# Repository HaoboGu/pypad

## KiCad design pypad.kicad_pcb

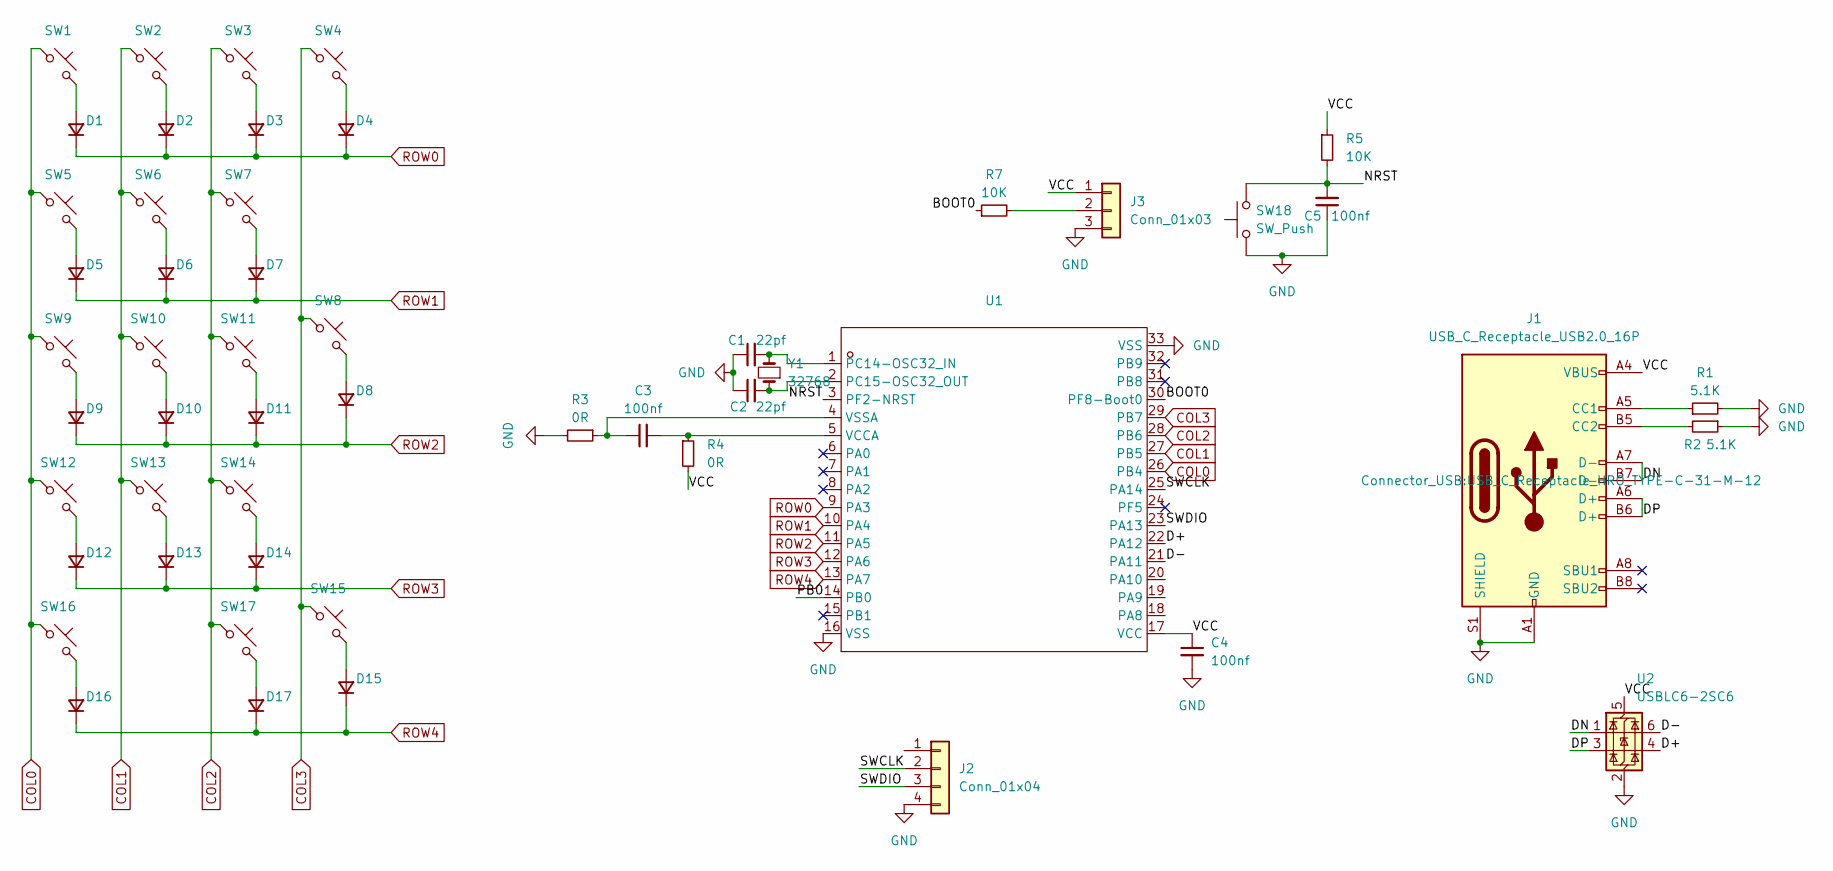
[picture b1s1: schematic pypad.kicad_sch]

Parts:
C1, C2: 22pf; C_0603_1608Metric
C3, C4, C5: 100nf; C_0603_1608Metric
D1, D2, D3, D4, D5, D6, D7, D8, D9, D10, D11, D12, D13, D14, D15, D16, D17: D; D_SOD-123F
J1: USB_C_Receptacle_USB2.0_16P; USB_C_Receptacle_HRO_TYPE-C-31-M-12
J2: Conn_01x04; PinHeader_1x04_P2.54mm_Vertical
J3: Conn_01x03; PinHeader_1x03_P2.54mm_Vertical
R1, R2: 5.1K; R_0603_1608Metric_Pad0.98x0.95mm_HandSolder
R3, R4: 0R; R_0603_1608Metric_Pad0.98x0.95mm_HandSolder
R5, R7: 10K; R_0603_1608Metric_Pad0.98x0.95mm_HandSolder
SW1, SW2, SW3, SW4, SW5, SW6, SW7, SW8, SW9, SW10, SW11, SW12, SW13, SW14, SW15, SW16, SW17: SW_Push; SW_Cherry_MX_PCB_1.00u
SW18: SW_Push; SW_SPST_PTS810
U1: QFN-32_L5.0-W5.0-P0.50-TL-EP3.5; Manufacturer Part PY32F071K1BU; LCSC Part Name PY32F071K1BU
U2: USBLC6-2SC6; SOT-23-6
Y1: 32768; Crystal_SMD_EuroQuartz_EQ161-2Pin_3.2x1.5mm

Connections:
/BOOT0: R7.1, U1.30 (PF8-Boot0)
/D+: U1.22 (PA12), U2.4 (I/O2)
/D-: U1.21 (PA11), U2.6 (I/O1)
/DN: J1.A7 (D-), J1.B7 (D-), U2.1 (I/O1)
/DP: J1.A6 (D+), J1.B6 (D+), U2.3 (I/O2)
/NRST: C5.2, R5.2, SW18.2, U1.3 (PF2-NRST)
/PB0: U1.14 (PB0)
/SWCLK: J2.2, U1.25 (PA14)
/SWDIO: J2.3, U1.23 (PA13)
/VCC: C4.1, J1.A4 (VBUS), J1.A9 (VBUS), J1.B4 (VBUS), J1.B9 (VBUS), J3.1, R4.2, R5.1, U1.17 (VCC), U2.5 (VBUS)
COL0: SW1.1, SW5.1, SW9.1, SW12.1, SW16.1, U1.26 (PB4)
COL1: SW2.1, SW6.1, SW10.1, SW13.1, U1.27 (PB5)
COL2: SW3.1, SW7.1, SW11.1, SW14.1, SW17.1, U1.28 (PB6)
COL3: SW4.1, SW8.1, SW15.1, U1.29 (PB7)
GND: C1.1, C2.1, C4.2, C5.1, J1.A1 (GND), J1.A12 (GND), J1.B1 (GND), J1.B12 (GND), J1.S1 (SHIELD), J2.4, J3.3, R1.2, R2.1, R3.2, SW18.1, U1.16 (VSS), U1.33 (VSS), U2.2 (GND)
unnamed: D1.2 (A), SW1.2
unnamed: D2.2 (A), SW2.2
unnamed: D3.2 (A), SW3.2
unnamed: D4.2 (A), SW4.2
unnamed: D5.2 (A), SW5.2
unnamed: D6.2 (A), SW6.2
unnamed: D7.2 (A), SW7.2
unnamed: D8.2 (A), SW8.2
unnamed: D9.2 (A), SW9.2
unnamed: D10.2 (A), SW10.2
unnamed: D11.2 (A), SW11.2
unnamed: D12.2 (A), SW12.2
unnamed: D13.2 (A), SW13.2
unnamed: D14.2 (A), SW14.2
unnamed: D15.2 (A), SW15.2
unnamed: D16.2 (A), SW16.2
unnamed: D17.2 (A), SW17.2
unnamed: J1.A5 (CC1), R1.1
unnamed: J1.B5 (CC2), R2.2
unnamed: J3.2, R7.2
unnamed: C1.2, U1.1 (PC14-OSC32_IN), Y1.2
unnamed: C2.2, U1.2 (PC15-OSC32_OUT), Y1.1
unnamed: C3.2, R4.1, U1.5 (VCCA)
unnamed: C3.1, R3.1, U1.4 (VSSA)
ROW0: D1.1 (K), D2.1 (K), D3.1 (K), D4.1 (K), U1.9 (PA3)
ROW1: D5.1 (K), D6.1 (K), D7.1 (K), U1.10 (PA4)
ROW2: D8.1 (K), D9.1 (K), D10.1 (K), D11.1 (K), U1.11 (PA5)
ROW3: D12.1 (K), D13.1 (K), D14.1 (K), U1.12 (PA6)
ROW4: D15.1 (K), D16.1 (K), D17.1 (K), U1.13 (PA7)

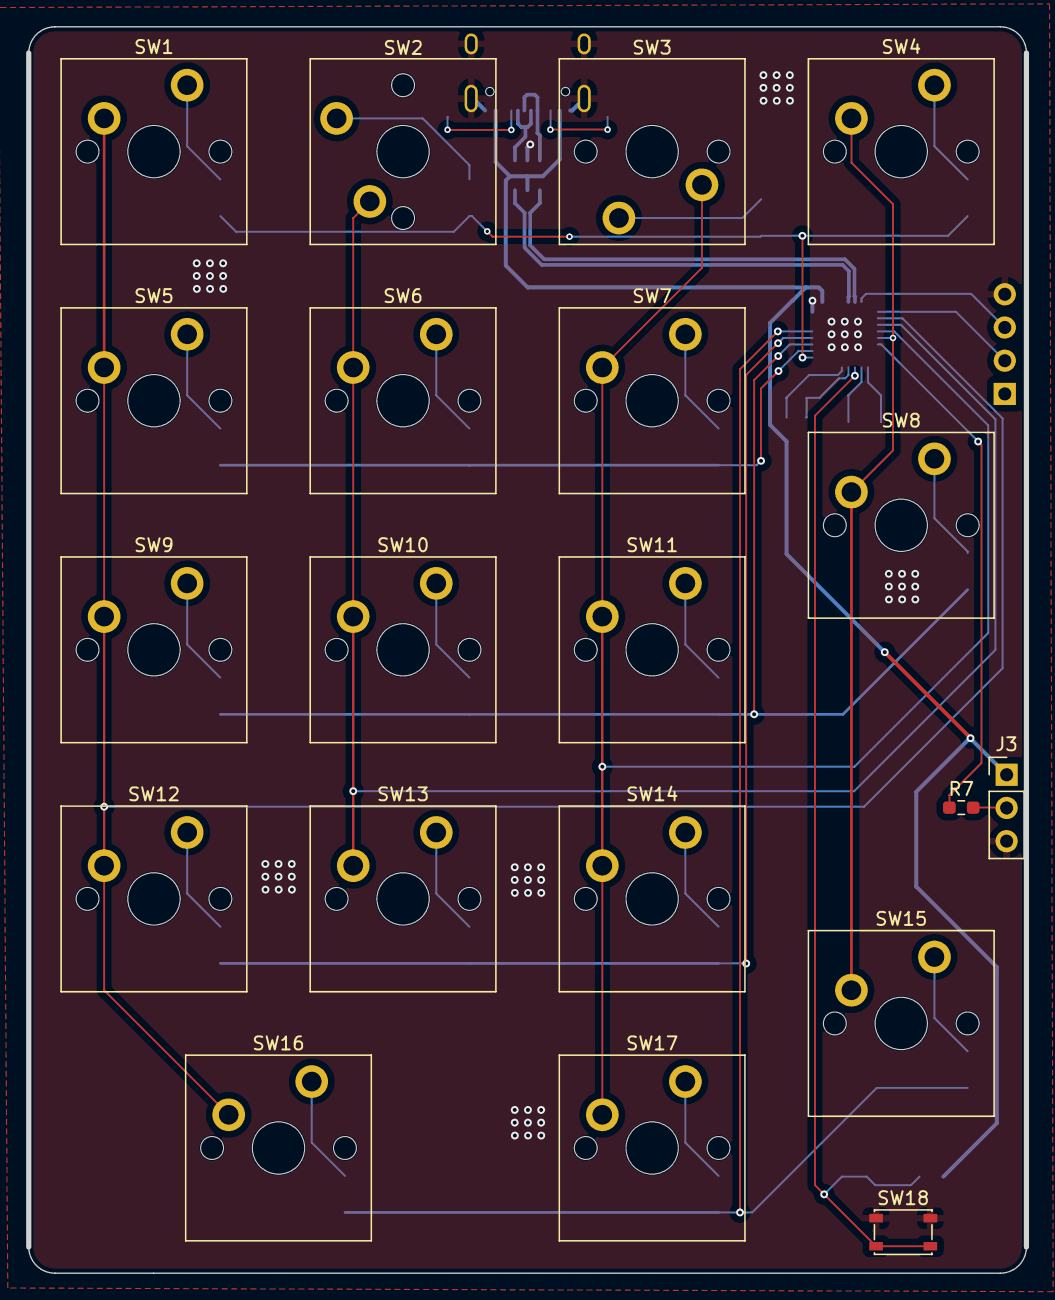
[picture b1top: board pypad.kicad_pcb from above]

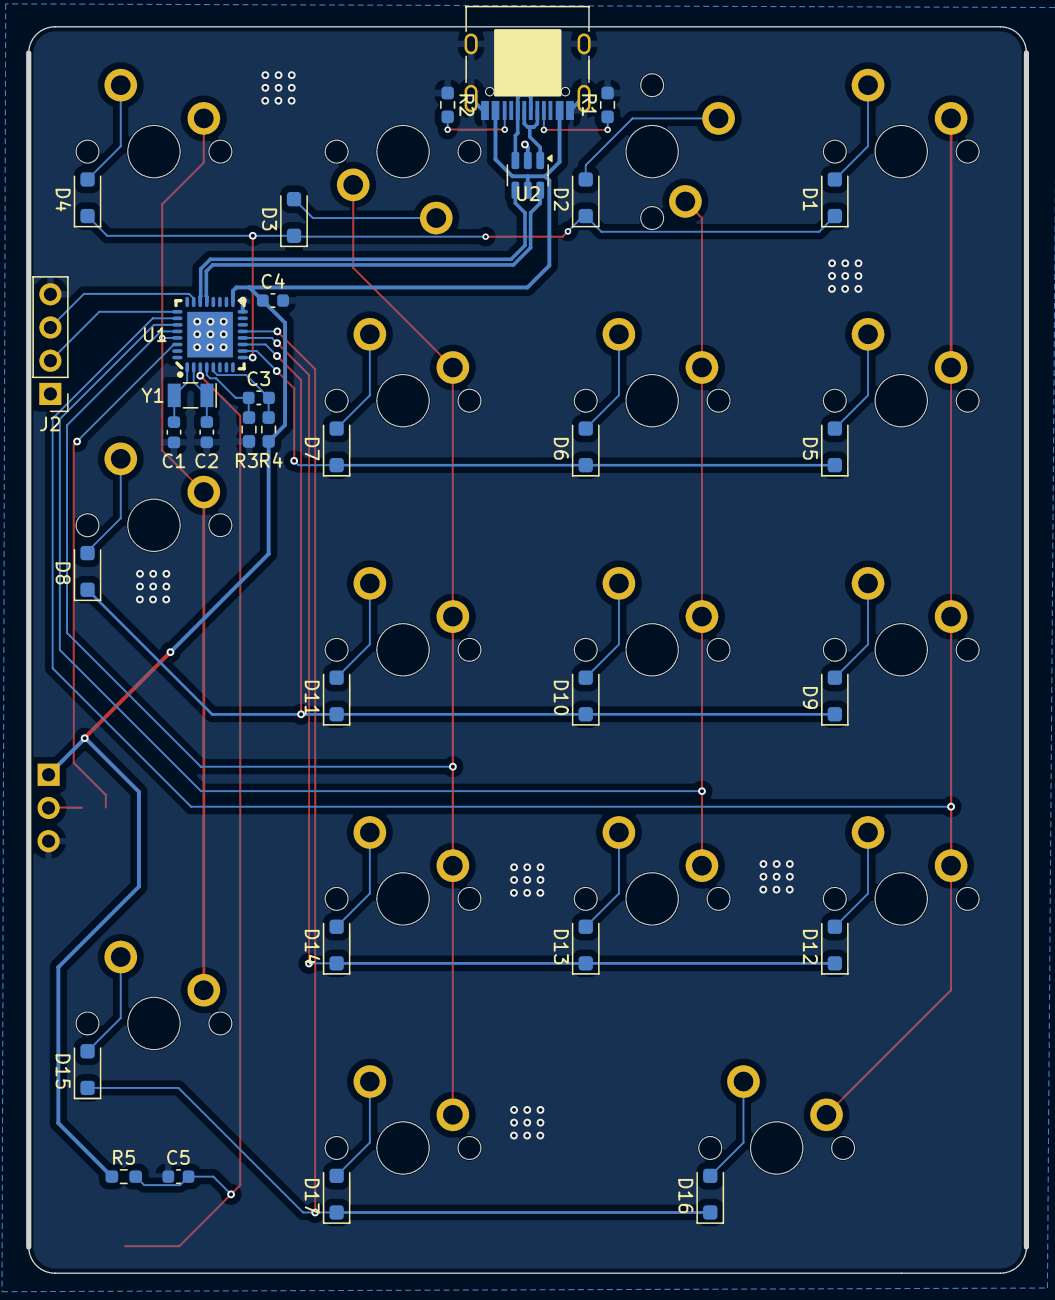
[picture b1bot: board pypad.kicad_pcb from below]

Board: 2 copper layers, 76.3 x 95.0 mm, 52 parts (32 on the bottom side), 43 nets.

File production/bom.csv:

Designator,Footprint,Quantity,Value,LCSC Part #
"C1, C2",0603,2,22pf,
"C3, C4, C5",0603,3,100nf,
"D1, D10, D11, D12, D13, D14, D15, D16, D17, D2, D3, D4, D5, D6, D7, D8, D9",D_SOD-123F,17,D,
J1,USB_C_Receptacle_HRO_TYPE-C-31-M-12,1,USB_C_Receptacle_USB2.0_16P,
J2,PinHeader_1x04_P2.54mm_Vertical,1,Conn_01x04,
J3,PinHeader_1x03_P2.54mm_Vertical,1,Conn_01x03,
"R1, R2",0603,2,5.1K,
"R3, R4",0603,2,0R,
"R5, R7",0603,2,10K,
"SW1, SW10, SW11, SW12, SW13, SW14, SW15, SW16, SW17, SW2, SW3, SW4, SW5, SW6, SW7, SW8, SW9",SW_Cherry_MX_PCB_1.00u,17,SW_Push,
SW18,SW_SPST_PTS810,1,SW_Push,
U1,QFN-32_L5.0-W5.0-P0.50-TL-EP3.5,1,~,
U2,SOT-23-6,1,USBLC6-2SC6,
Y1,Crystal_SMD_EuroQuartz_EQ161-2Pin_3.2x1.5mm,1,32768,

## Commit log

2025-03-05 add bom
